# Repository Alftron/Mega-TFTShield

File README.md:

# Arduino Mega-TFTShield

I was getting annoyed with the 3.5" HVGA shield hogging all the pins on a Mega 2560 so this is an interface board to free up some of the pins.

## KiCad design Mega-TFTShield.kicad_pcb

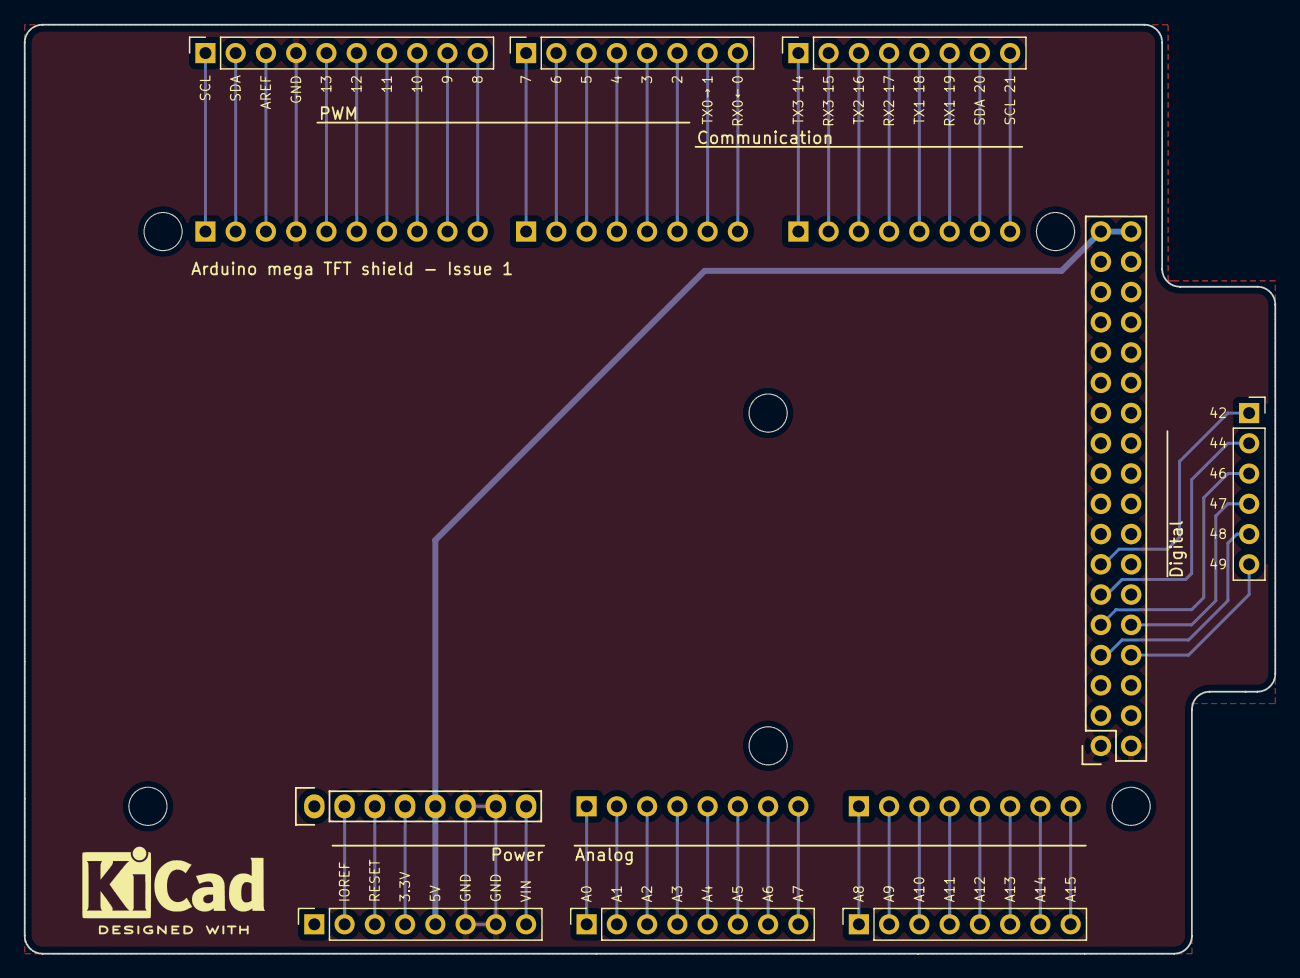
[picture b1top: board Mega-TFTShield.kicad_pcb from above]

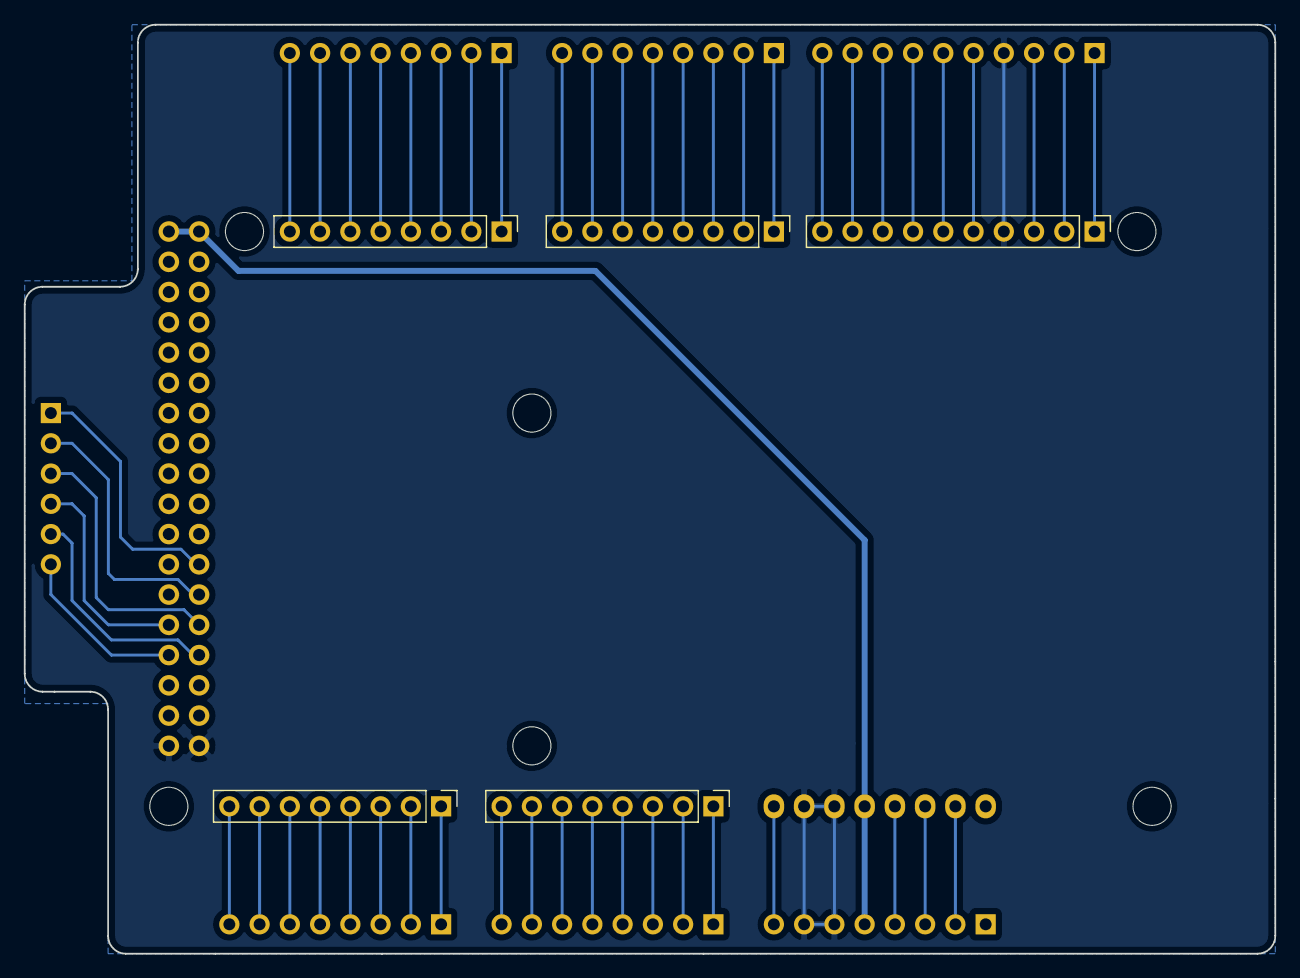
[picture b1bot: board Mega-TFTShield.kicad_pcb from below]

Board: 2 copper layers, 105.0 x 78.0 mm, 20 parts (5 on the bottom side), 53 nets.

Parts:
CN1: Power; Socket_Strip_Arduino_1x08
CN2, CN3: Analog; PinHeader_1x08_P2.54mm_Vertical
CN4: Digital; Socket_Strip_Arduino_2x18
CN5: PWM; PinHeader_1x10_P2.54mm_Vertical
CN6: PWM; PinHeader_1x08_P2.54mm_Vertical
CN7: Communication; PinHeader_1x08_P2.54mm_Vertical
CN8: Power; PinSocket_1x08_P2.54mm_Vertical
CN9, CN10: Analog; PinSocket_1x08_P2.54mm_Vertical
CN11: Digital; PinSocket_1x06_P2.54mm_Vertical
CN12: PWM; PinSocket_1x10_P2.54mm_Vertical
CN14: Communication; PinSocket_1x08_P2.54mm_Vertical
CNe: PWM; PinSocket_1x08_P2.54mm_Vertical
MNT1, MNT2, MNT3, MNT4, MNT5, MNT6: CONN_01X01; MountingHole_3.2mm_M3

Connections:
+3V3: CN1.4, CN8.4
+5V: CN1.5, CN4.35, CN4.36, CN8.5
/0(Rx0): CN6.8, CNe.8
/1(Tx0): CN6.7, CNe.7
/2(**): CN6.6, CNe.6
/3(**): CN6.5, CNe.5
/4(**): CN6.4, CNe.4
/5(**): CN6.3, CNe.3
/6(**): CN6.2, CNe.2
/7(**): CN6.1, CNe.1
/8(**): CN5.10, CN12.10
/9(**): CN5.9, CN12.9
/10(**): CN5.8, CN12.8
/11(**): CN5.7, CN12.7
/12(**): CN5.6, CN12.6
/13(**): CN5.5, CN12.5
/14(Tx3): CN7.1, CN14.1
/15(Rx3): CN7.2, CN14.2
/16(Tx2): CN7.3, CN14.3
/17(Rx2): CN7.4, CN14.4
/18(Tx1): CN7.5, CN14.5
/19(Rx1): CN7.6, CN14.6
/20(SDA): CN7.7, CN14.7
/21(SCL): CN7.8, CN14.8
/42: CN4.13, CN11.1
/44: CN4.11, CN11.2
/46: CN4.9, CN11.3
/47: CN4.10, CN11.4
/48: CN4.7, CN11.5
/49: CN4.8, CN11.6
/A0: CN2.1, CN9.1
/A1: CN2.2, CN9.2
/A2: CN2.3, CN9.3
/A3: CN2.4, CN9.4
/A4: CN2.5, CN9.5
/A5: CN2.6, CN9.6
/A6: CN2.7, CN9.7
/A7: CN2.8, CN9.8
/A8: CN3.1, CN10.1
/A9: CN3.2, CN10.2
/A10: CN3.3, CN10.3
/A11: CN3.4, CN10.4
/A12: CN3.5, CN10.5
/A13: CN3.6, CN10.6
/A14: CN3.7, CN10.7
/A15: CN3.8, CN10.8
/AREF: CN5.3, CN12.3
/IOREF: CN1.2, CN8.2
/Reset: CN1.3, CN8.3
/SCL: CN5.1, CN12.1
/SDA: CN5.2, CN12.2
/Vin: CN1.8, CN8.8
GND: CN1.6, CN1.7, CN4.1, CN4.2, CN5.4, CN8.6, CN8.7, CN12.4

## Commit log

2020-03-18 Adding picture of hardware
2020-03-18 Update README.md
    Adding example hardware to readme
